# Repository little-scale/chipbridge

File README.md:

# Chipbridge

Chipbridge is a shared RP2040-based MIDI and synchronisation interface for
retro-console music systems. A common RP2040-Zero board provides USB MIDI,
opto-isolated serial MIDI, status indication, and a protected two-wire console
interface. Console-specific cables and passive adapters connect that interface
to supported systems.

This repository owns the shared Chipbridge hardware and RP2040 firmware. Atari
Lynx and Atari 2600 firmware remain in their respective software projects; this
repository contains only their applicable shared hardware and adapters.

## Compatibility

In this table, **Sync** means synchronisation from MIDI Clock. **Notes** means
MIDI note events are delivered to the relevant tracker channel or instrument
inputs.

| Console | Software | Sync | Notes | PCB | Firmware | Control input | Test |
|---|---|---:|---:|---|---|---|---|
| Sega Master System | [SMSGGDJ tracker](https://github.com/little-scale/smsggdj) | Yes | Yes | Shared | Shared | Sega 9-pin | OK |
| Mega Drive / Genesis | [genmddj tracker](https://github.com/little-scale/genmddj) | Yes | Yes | Shared | Shared | Sega 9-pin | OK |
| Game Gear | [SMSGGDJ tracker](https://github.com/little-scale/smsggdj) | Yes | Yes | Shared | Shared | Game Gear sync PCB | OK |
| Atari Lynx | [alynxdj tracker](https://github.com/little-scale/alynxdj) | Yes | Yes | Shared | Target-specific | 2.5 mm cable | OK |
| Super Nintendo | [SNDJ tracker](https://github.com/little-scale/sndj) | Yes | No | Shared | Shared | SNES cable | OK |
| Atari 2600 | [a26f-neo interface](https://github.com/little-scale/a26f-neo) | No | Yes | Shared | Target-specific | Atari 9-pin PCB | OK |

“Shared” means the component is maintained in Chipbridge. Target-specific
firmware remains in its console software project. See the
[`compatibility notes`](docs/COMPATIBILITY.md) for the ownership boundary.

For Wi-Fi Ableton Link rather than wired MIDI, see the complementary
[SMSGGDJ Link ESP32 bridge](https://github.com/little-scale/smsggdj-link-esp32).

## Repository layout

- `firmware/rp2040/` — shared Pico-family firmware and build instructions.
- `hardware/main/` — the RP2040-Zero Chipbridge board; see the
  [bill of materials](hardware/BOM.md).
- `hardware/adapters/` — console connector and cable adapter PCBs.
- `docs/` — MIDI protocol, serial-MIDI circuit, and wiring documentation.
- `releases/rp2040/` — current prebuilt UF2 images.
- `tests/` — host-side protocol/parser tests.
- `tools/` — reproducible release builders.

## Licensing

- Hardware designs: CERN-OHL-P-2.0.
- Firmware, tools, tests, and corresponding UF2 binaries: GPL-2.0-only.
- Documentation: CC BY 4.0.

See [`LICENSE.md`](LICENSE.md) for the precise scope, attribution, and licence
texts.

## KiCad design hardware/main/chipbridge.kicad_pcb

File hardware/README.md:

# Chipbridge hardware

## Projects

- `main/` — shared RP2040-Zero Chipbridge board.
- `adapters/game-gear/` — Game Gear EXT-port adapter.
- `adapters/sega-9pin/` — Sega 9-pin controller-port adapter.
- `adapters/atari-9pin/` — Atari 9-pin adapter.

Each directory contains the editable KiCad project, schematic, and PCB layout.
KiCad automatic backups, lock files, history, and per-user project state are
intentionally excluded.

## Bill of materials

See the [Chipbridge bill of materials](BOM.md) for the main board and adapter
parts lists. Price-free CSV exports are also provided alongside each KiCad
project. The component properties in the schematics are the source of truth.

## Project-local libraries

The main board uses a custom Waveshare RP2040-Zero symbol and footprint under
`libraries/`. Its `sym-lib-table` and `fp-lib-table` use `${KIPRJMOD}` relative
paths while retaining the original library nicknames used by the schematic and
PCB. No global or user-specific KiCad library entry is required.

The adapter projects currently use standard KiCad libraries only.

## Licensing

The KiCad schematics, PCB layouts, and project-local hardware libraries in
this directory are licensed under the permissive
[CERN Open Hardware Licence Version 2 – Permissive](LICENSE-CERN-OHL-P-2.0.txt),
SPDX identifier `CERN-OHL-P-2.0`.

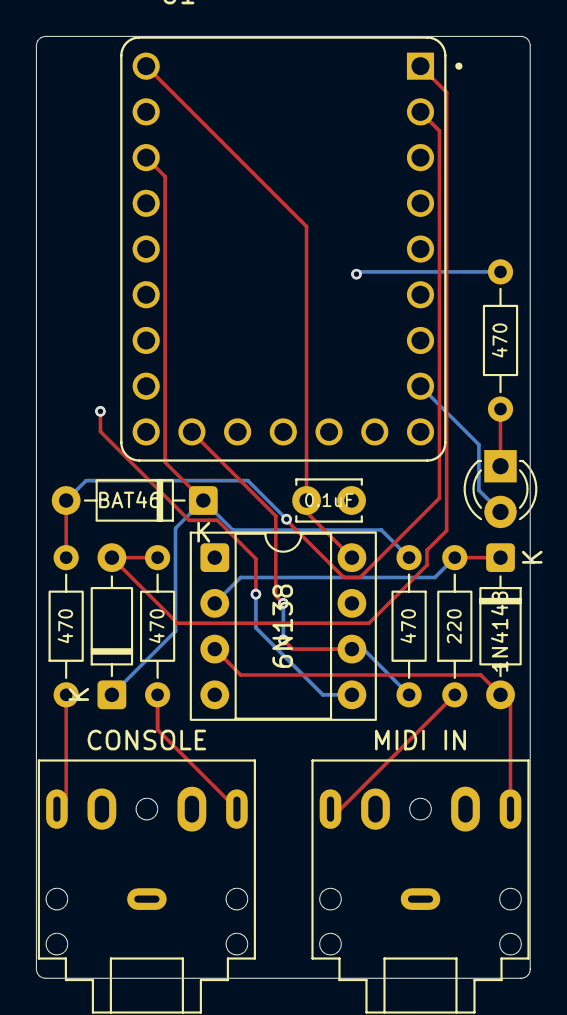
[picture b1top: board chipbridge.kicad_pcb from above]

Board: 2 copper layers, 27.4 x 52.3 mm, 14 parts (0 on the bottom side), 13 nets.

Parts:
C1: 0.1uF; C_Disc_D3.4mm_W2.1mm_P2.50mm
CONSOLE: CONSOLE_DATA; Jack_3.5mm_CUI_SJ1-3525N_Horizontal
D1, D2: BAT46; D_DO-35_SOD27_P7.62mm_Horizontal
D3: 1N4148; D_DO-35_SOD27_P7.62mm_Horizontal
D4: LED; LED_D3.0mm
MIDI IN: TRS_MIDI_IN; Jack_3.5mm_CUI_SJ1-3525N_Horizontal
R1, R2, R4, R5: 470; R_Axial_DIN0204_L3.6mm_D1.6mm_P7.62mm_Horizontal
R3: 220; R_Axial_DIN0204_L3.6mm_D1.6mm_P7.62mm_Horizontal
U1: RP2040-ZERO; MODULE_RP2040-ZERO
U2: 6N138; DIP-8_W7.62mm_Socket

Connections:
+3V3: D1.1 (K), D2.1 (K), R4.1, U1.21 (3V3)
+5V: C1.1, U1.23 (5V), U2.8 (VCC)
/DATA0: CONSOLE.T, R1.1
/DATA1: CONSOLE.R, R2.1
/MIDI_DATA: R4.2, U1.14 (GP13), U2.6 (VO2)
GND: C1.2, CONSOLE.S, R5.1, U1.22 (GND), U2.5 (GND)
unnamed: D1.2 (A), R1.2, U1.1 (GP0)
unnamed: D2.2 (A), R2.2, U1.2 (GP1)
unnamed: D3.2 (A), MIDI IN.T, U2.3 (C2)
unnamed: D3.1 (K), R3.2, U2.2 (C1)
unnamed: D4.2 (A), U1.8 (GP7)
unnamed: D4.1 (K), R5.2
unnamed: MIDI IN.R, R3.1

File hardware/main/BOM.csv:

Reference,Qty,Value,Footprint,MPN,Manufacturer,Chosen_Distributor,Datasheet,Validated,DNP,Notes
C1,1,0.1uF,Disc_D3.4mm_W2.1mm_P2.50mm,,,,,,,"Generic 100 nF ceramic capacitor, 16 V minimum, 2.50 mm lead pitch, body no larger than footprint"
"D1,D2",2,BAT46,DO-35_SOD27_P7.62mm_Horizontal,BAT46-TAP,Vishay,,https://www.vishay.com/docs/85662/bat46.pdf,,,
D3,1,1N4148,DO-35_SOD27_P7.62mm_Horizontal,1N4148,onsemi,,https://www.onsemi.com/pdf/datasheet/1n914-d.pdf,,,
D4,1,LED,LED_D3.0mm,,,,,,,Generic 3 mm through-hole indicator LED; observe polarity
J1,1,CONSOLE_DATA,Jack_3.5mm_CUI_SJ1-3525N_Horizontal,SJ1-3525N,Same Sky,,https://www.sameskydevices.com/product/resource/sj1-352xn.pdf,,,
J2,1,TRS_MIDI_IN,Jack_3.5mm_CUI_SJ1-3525N_Horizontal,SJ1-3525N,Same Sky,,https://www.sameskydevices.com/product/resource/sj1-352xn.pdf,,,
"R2,R4,R1,R5",4,470r,Axial_DIN0204_L3.6mm_D1.6mm_P7.62mm_Horizontal,,,,,,,"Generic 470 ohm axial resistor, 0.25 W or greater, DIN0204 body"
R3,1,220r,Axial_DIN0204_L3.6mm_D1.6mm_P7.62mm_Horizontal,,,,,,,"Generic 220 ohm axial resistor, 0.25 W or greater, DIN0204 body"
U1,1,RP2040-ZERO,MODULE_RP2040-ZERO,RP2040-ZERO,Waveshare Electronics,,https://www.waveshare.com/wiki/RP2040-Zero,,,
U2,1,6N138,DIP-8_W7.62mm_Socket,6N138M,onsemi,,https://www.onsemi.com/download/data-sheet/pdf/hcpl2731m-d.pdf,,,8-pin DIP optocoupler; a DIP-8 socket is optional and is not included in this BOM
